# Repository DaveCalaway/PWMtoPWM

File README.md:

# PWMtoPWM

In that repo we have 2 project:
- **pwmTOpwm**: example with potentiometer
  - Status: Stable.
  - No Kicad board
- **pwmTOpwm_dual**: example with encoder
  - Status: pre Release candidate
  - Kicad board

  Dave Calaway.

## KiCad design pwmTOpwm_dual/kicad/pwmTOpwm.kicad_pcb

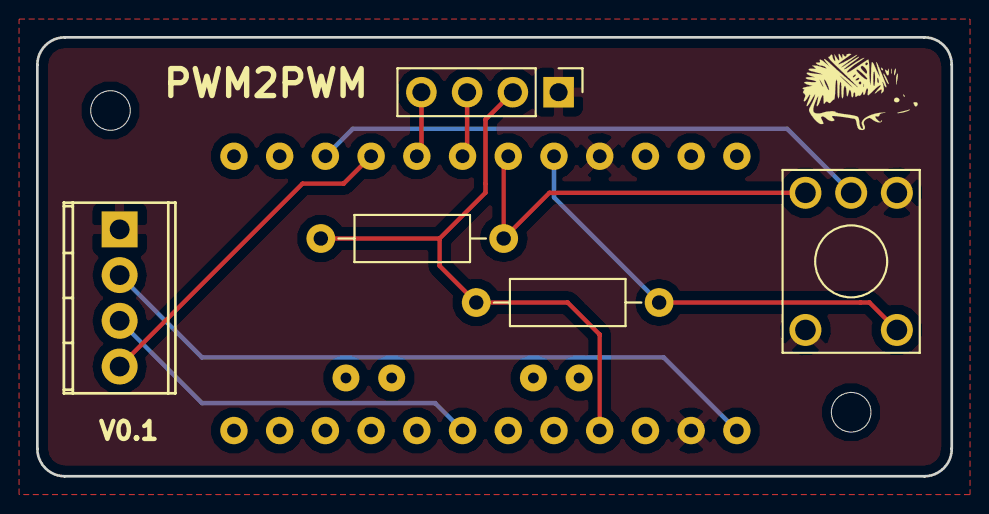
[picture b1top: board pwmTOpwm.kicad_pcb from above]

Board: 2 copper layers, 50.8 x 24.4 mm, 6 parts (0 on the bottom side), 10 nets.

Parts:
J1: Conn_01x04; Pin_Header_Straight_1x04_Pitch2.54mm
J2: Screw_Terminal_01x04; TerminalBlock_Phoenix_MPT-2.54mm_4pol
R1, R2: 10k; R_Axial_DIN0207_L6.3mm_D2.5mm_P10.16mm_Horizontal
SW1: Rotary_Encoder_Switch; KSA_Tactile_SPST
uP1: ARDUPROMINI-6; ArduProMini-6

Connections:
/A: R2.2, SW1.1, uP1.11
/B: R1.2, SW1.3, uP1.12
/SCL: J1.3, uP1.13
/SDA: J1.4, uP1.14
/VCC: J1.2, R1.1, R2.1, uP1.22
/Vin: J2.2, uP1.19
/button: SW1.4, uP1.16
/pwm_in: J2.3, uP1.25
/pwm_out: J2.4, uP1.15
GND: J1.1, J2.1, SW1.2, SW1.5, uP1.10, uP1.20

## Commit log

2018-05-18 init
    bug in the little Vpot measurements
2018-05-19 Beta + schematic
2018-05-19 Auto stash before merge of "master" and "origin/master"
2018-05-23 single number display fixed
2018-07-10 potentiometer version
2018-07-10 Auto stash before rebase of "origin/master"
2018-07-10 Code Optimized
2018-07-11 improved fast response
2018-07-17 Laser sim added
